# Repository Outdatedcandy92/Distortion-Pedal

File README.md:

# Distortion Pedal

A tiny distortion pedal PCB designed to be embedded inside a guitar. The board uses 1206 and THT components making it easily moddable; in addition it also includes pin sockets for transistors and op amp making it easy to swap out and try different components for different sounds!

---

## Schematics

Schematics pdf is available under the `/PCB` folder and the project's KiCad files can be found under `/PCB/kicad`.

---

## PCB

---

## License

This project is licensed under the CERN Open Hardware Licence Version 2 Weakly Reciprocal [(CERN OHL W)](LICENSE.txt)

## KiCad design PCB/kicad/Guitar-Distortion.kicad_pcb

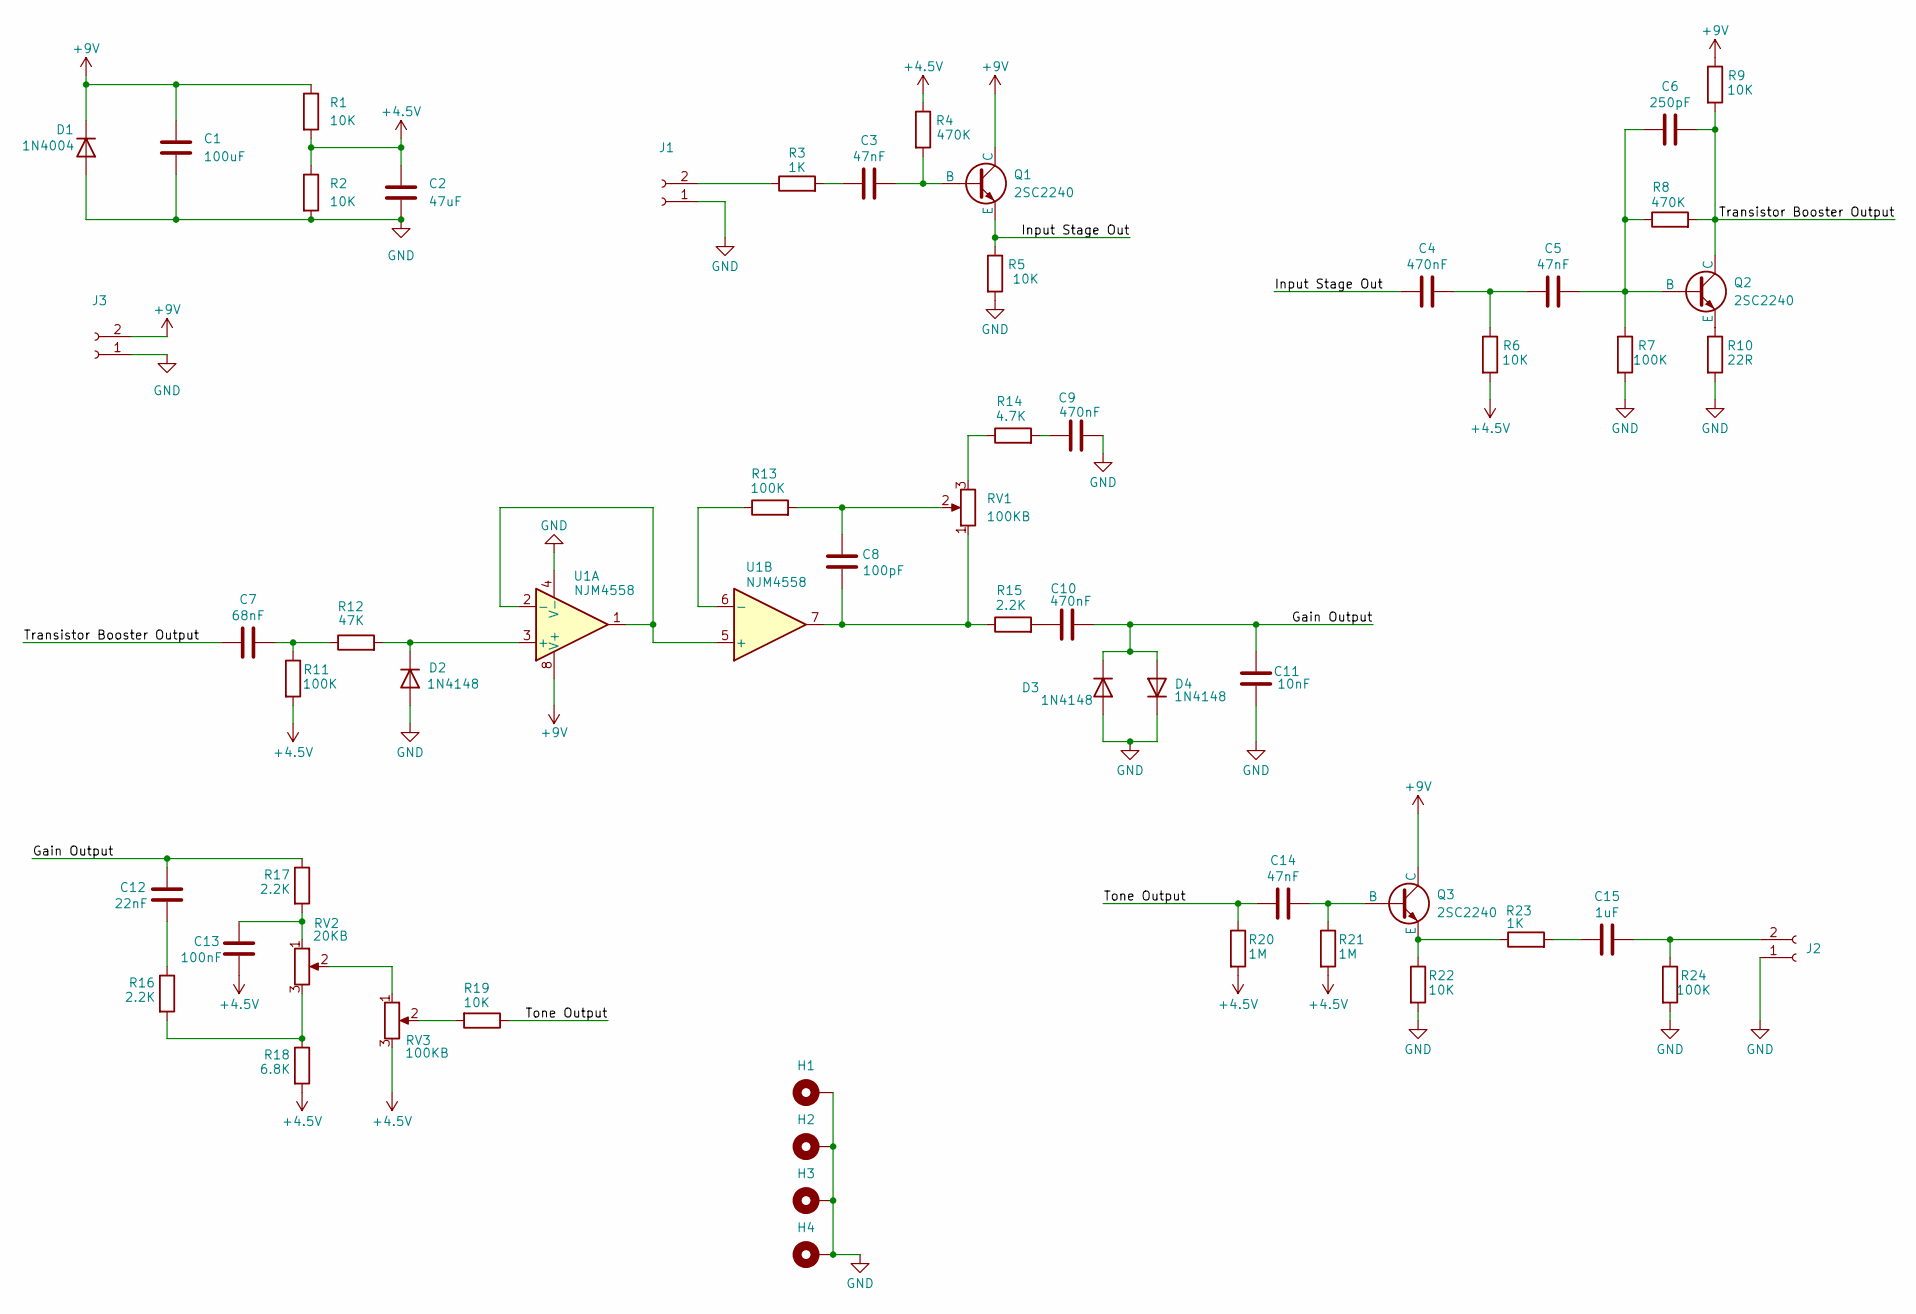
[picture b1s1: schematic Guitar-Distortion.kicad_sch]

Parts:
C1: 100uF; CP_Elec_6.3x7.7; LCSC ID C72478
C2: 47uF; CP_Elec_6.3x7.7; LCSC ID C72523
C3, C5, C14: 47nF; C_Axial_L3.8mm_D2.6mm_P7.50mm_Horizontal; LCSC ID C46638908
C4, C9, C10: 470nF; C_Axial_L3.8mm_D2.6mm_P7.50mm_Horizontal; LCSC ID C3019096
C6: 250pF; C_Axial_L3.8mm_D2.6mm_P7.50mm_Horizontal; LCSC ID C49450688
C7: 68nF; C_Axial_L3.8mm_D2.6mm_P7.50mm_Horizontal; LCSC ID C2928859
C8: 100pF; C_Axial_L3.8mm_D2.6mm_P7.50mm_Horizontal; LCSC ID C3793359
C11: 10nF; C_Axial_L3.8mm_D2.6mm_P7.50mm_Horizontal; LCSC ID C390071
C12: 22nF; C_Axial_L3.8mm_D2.6mm_P7.50mm_Horizontal; LCSC ID C390073
C13: 100nF; C_Axial_L3.8mm_D2.6mm_P7.50mm_Horizontal; LCSC ID C506826
C15: 1uF; C_Axial_L3.8mm_D2.6mm_P7.50mm_Horizontal; LCSC ID C46596148
D1: 1N4004; D_DO-35_SOD27_P7.62mm_Horizontal; LCSC ID C511070
D2, D3, D4: 1N4148; D_DO-35_SOD27_P7.62mm_Horizontal; LCSC ID C84410
H1, H2, H3, H4: MountingHole_Pad; MountingHole_3.2mm_M3_DIN965_Pad
J1, J2, J3: Conn_01x02_Socket; JST_XH_B2B-XH-A_1x02_P2.50mm_Vertical; LCSC ID C158012
Q1, Q2, Q3: 2SC2240; PinSocket_1x03_P2.54mm_Vertical; LCSC ID C328606
R1, R2, R5, R6, R9, R19, R22: 10K; R_1206_3216Metric; LCSC ID C17902
R3, R23: 1K; R_1206_3216Metric; LCSC ID C4410
R4, R8: 470K; R_1206_3216Metric; LCSC ID C17997
R7, R11, R13, R24: 100K; R_1206_3216Metric; LCSC ID C17900
R10: 22R; R_1206_3216Metric; LCSC ID C17958
R12: 47K; R_1206_3216Metric; LCSC ID C25833
R14: 4.7K; R_1206_3216Metric; LCSC ID C17936
R15, R16, R17: 2.2K; R_1206_3216Metric; LCSC ID C17948
R18: 6.8K; R_1206_3216Metric; LCSC ID C26046
R20, R21: 1M; R_1206_3216Metric; LCSC ID C17927
RV1, RV3: 100KB; JST_PH_B3B-PH-K_1x03_P2.00mm_Vertical; LCSC ID C131339
RV2: 20KB; JST_PH_B3B-PH-K_1x03_P2.00mm_Vertical; LCSC ID C131339
U1: NJM4558; DIP-8_W7.62mm_Socket; LCSC ID C72129

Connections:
+4.5V: C2.1, C13.1, R1.2, R2.1, R4.1, R6.2, R11.2, R18.2, R20.2, R21.2, RV3.3
+9V: C1.1, D1.1 (K), J3.2, Q1.2 (C), Q3.2 (C), R1.1, R9.1, U1.8 (V+)
/Gain Output: C10.2, C11.1, C12.2, D3.1 (K), D4.2 (A), R17.1
/Input Stage Out: C4.1, Q1.3 (E), R5.1
/Tone Output: C14.1, R19.1, R20.1
/Transistor Booster Output: C6.2, C7.1, Q2.2 (C), R8.2, R9.2
GND: C1.2, C2.2, C9.2, C11.2, D1.2 (A), D2.2 (A), D3.2 (A), D4.1 (K), H1.1, H2.1, H3.1, H4.1, J1.1, J2.1, J3.1, R2.2, R5.2, R7.2, R10.2, R22.2, R24.2, U1.4 (V-)
unnamed: C3.1, R3.2
unnamed: C4.2, C5.1, R6.1
unnamed: C7.2, R11.1, R12.1
unnamed: C8.1, R13.2, RV1.2
unnamed: C8.2, R15.1, RV1.1, U1.7
unnamed: C9.1, R14.2
unnamed: C10.1, R15.2
unnamed: C12.1, R16.1
unnamed: C13.2, R17.2, RV2.1
unnamed: C15.1, R23.2
unnamed: D2.1 (K), R12.2, U1.3 (+)
unnamed: J1.2, R3.1
unnamed: C15.2, J2.2, R24.1
unnamed: C3.2, Q1.1 (B), R4.2
unnamed: C5.2, C6.1, Q2.1 (B), R7.1, R8.1
unnamed: Q2.3 (E), R10.1
unnamed: C14.2, Q3.1 (B), R21.1
unnamed: Q3.3 (E), R22.1, R23.1
unnamed: R14.1, RV1.3
unnamed: R16.2, R18.1, RV2.3
unnamed: R19.2, RV3.2
unnamed: RV2.2, RV3.1
unnamed: U1.1, U1.2 (-), U1.5 (+)
unnamed: R13.1, U1.6 (-)

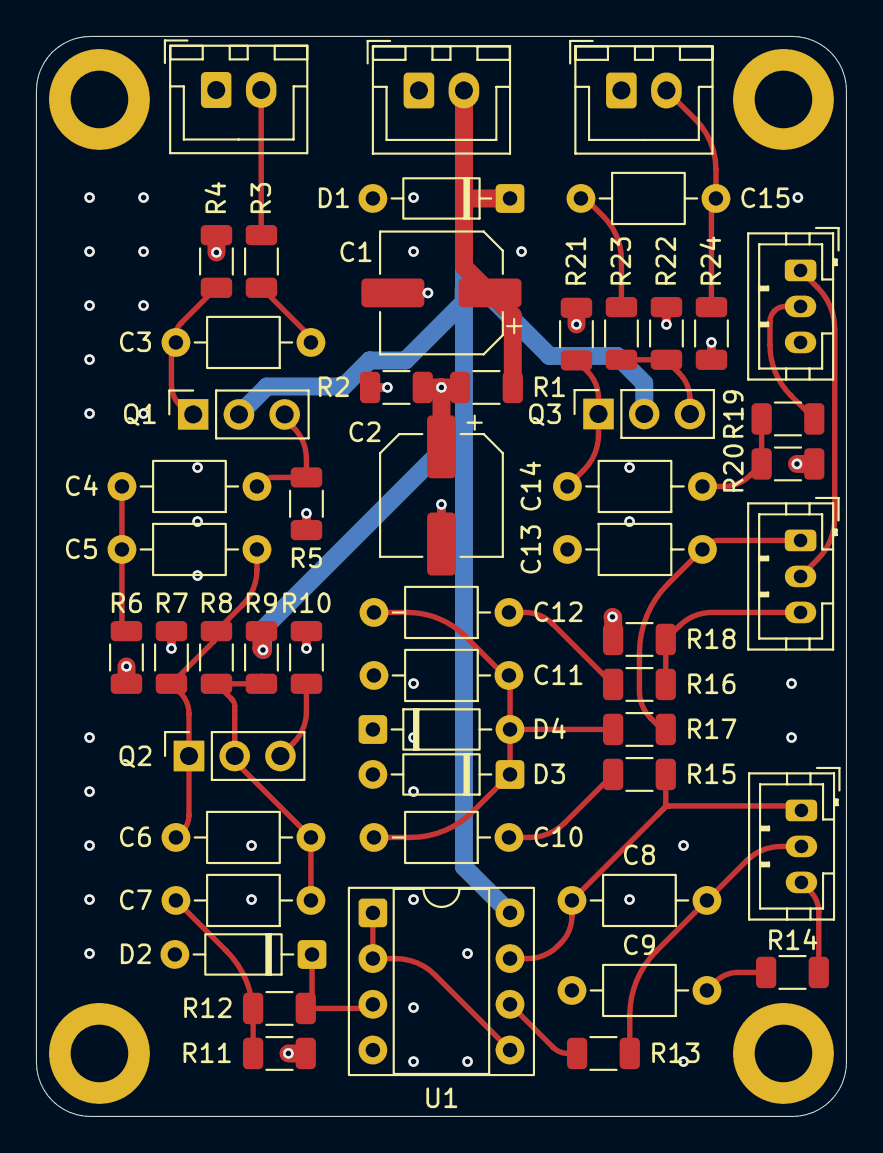
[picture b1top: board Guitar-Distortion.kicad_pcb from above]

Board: 4 copper layers, 45.0 x 60.0 mm, 57 parts (0 on the bottom side), 31 nets.

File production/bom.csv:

"Reference","Qty","Value","LCSC ID","Footprint"
"C8","1","100pF","C3793359","Capacitor_THT:C_Axial_L3.8mm_D2.6mm_P7.50mm_Horizontal"
"C6","1","250pF","C49450688","Capacitor_THT:C_Axial_L3.8mm_D2.6mm_P7.50mm_Horizontal"
"C11","1","10nF","C390071","Capacitor_THT:C_Axial_L3.8mm_D2.6mm_P7.50mm_Horizontal"
"C12","1","22nF","C390073","Capacitor_THT:C_Axial_L3.8mm_D2.6mm_P7.50mm_Horizontal"
"C3,C5,C14","3","47nF","C46638908","Capacitor_THT:C_Axial_L3.8mm_D2.6mm_P7.50mm_Horizontal"
"C7","1","68nF","C2928859","Capacitor_THT:C_Axial_L3.8mm_D2.6mm_P7.50mm_Horizontal"
"C13","1","100nF","C506826","Capacitor_THT:C_Axial_L3.8mm_D2.6mm_P7.50mm_Horizontal"
"C4,C9,C10","3","470nF","C3019096","Capacitor_THT:C_Axial_L3.8mm_D2.6mm_P7.50mm_Horizontal"
"C15","1","1uF","C46596148","Capacitor_THT:C_Axial_L3.8mm_D2.6mm_P7.50mm_Horizontal"
"C2","1","47uF","C72523","Capacitor_SMD:CP_Elec_6.3x7.7"
"C1","1","100uF","C72478","Capacitor_SMD:CP_Elec_6.3x7.7"
"RV2","1","20KB","C131339","Connector_JST:JST_PH_B3B-PH-K_1x03_P2.00mm_Vertical"
"R10","1","22R","C17958","Resistor_SMD:R_1206_3216Metric"
"RV1,RV3","2","100KB","C131339","Connector_JST:JST_PH_B3B-PH-K_1x03_P2.00mm_Vertical"
"R3,R23","2","1K","C4410","Resistor_SMD:R_1206_3216Metric"
"R15,R16,R17","3","2.2K","C17948","Resistor_SMD:R_1206_3216Metric"
"R14","1","4.7K","C17936","Resistor_SMD:R_1206_3216Metric"
"R18","1","6.8K","C26046","Resistor_SMD:R_1206_3216Metric"
"R1,R2,R5,R6,R9,R19,R22","7","10K","C17902","Resistor_SMD:R_1206_3216Metric"
"R12","1","47K","C25833","Resistor_SMD:R_1206_3216Metric"
"R7,R11,R13,R24","4","100K","C17900","Resistor_SMD:R_1206_3216Metric"
"R4,R8","2","470K","C17997","Resistor_SMD:R_1206_3216Metric"
"R20,R21","2","1M","C17927","Resistor_SMD:R_1206_3216Metric"
"D1","1","1N4004","C511070","Diode_THT:D_DO-35_SOD27_P7.62mm_Horizontal"
"D2,D3,D4","3","1N4148","C84410","Diode_THT:D_DO-35_SOD27_P7.62mm_Horizontal"
"Q1,Q2,Q3","3","2SC2240","C328606","Connector_PinSocket_2.54mm:PinSocket_1x03_P2.54mm_Vertical"
"J1,J2,J3","3","Conn_01x02_Socket","C158012","Connector_JST:JST_XH_B2B-XH-A_1x02_P2.50mm_Vertical"
"H1,H2,H3,H4","4","MountingHole_Pad","-","MountingHole:MountingHole_3.2mm_M3_DIN965_Pad"
"U1","1","NJM4558","C72129","Package_DIP:DIP-8_W7.62mm_Socket"

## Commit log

2026-03-10 local image + journal update
2026-03-10 fix image
2026-03-10 fix image format
2026-03-10 actually fixed images
